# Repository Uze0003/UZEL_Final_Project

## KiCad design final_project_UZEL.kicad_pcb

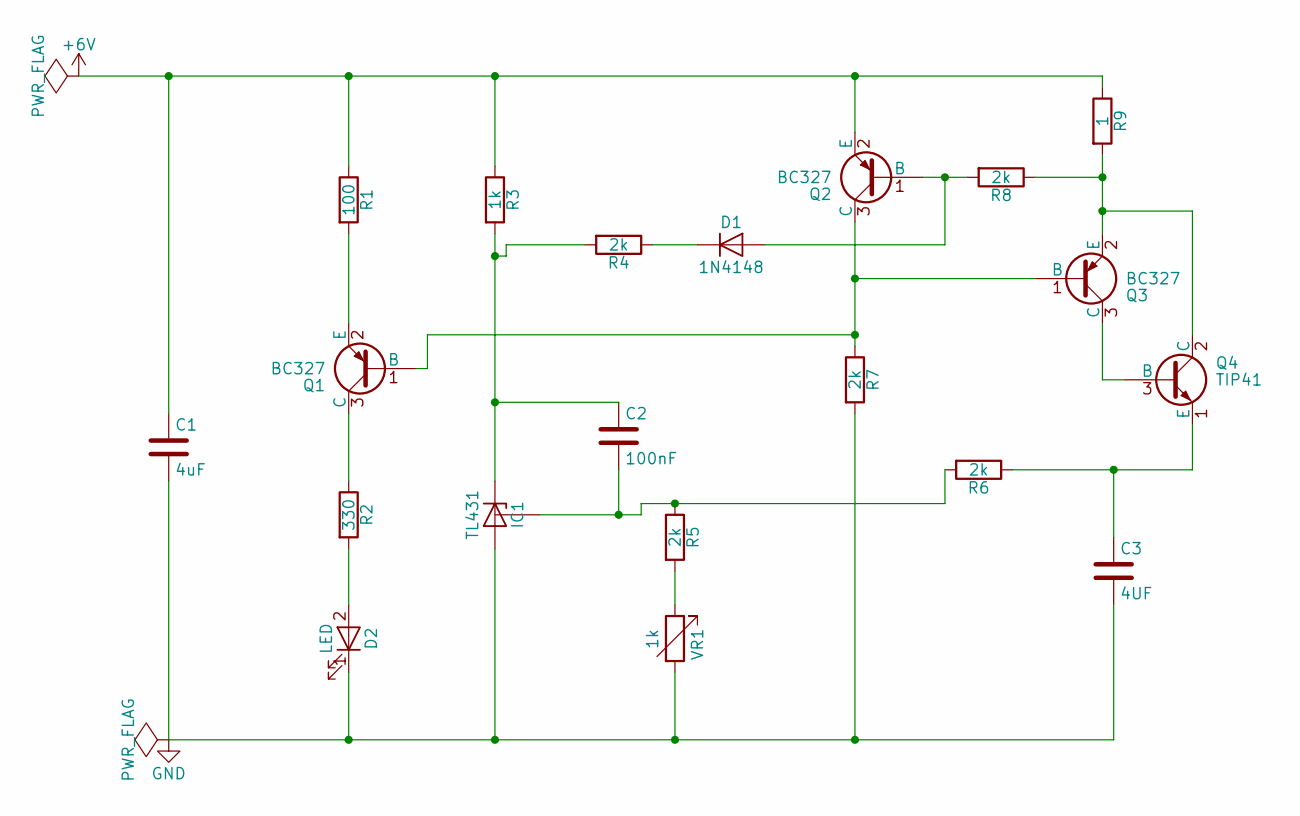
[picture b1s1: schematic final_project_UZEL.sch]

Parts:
C1: 4uF; C_Axial_L12.0mm_D6.5mm_P15.00mm_Horizontal
C2: 100nF; CP_Axial_L11.0mm_D8.0mm_P15.00mm_Horizontal
C3: 4UF; C_Axial_L12.0mm_D6.5mm_P15.00mm_Horizontal
D1: 1N4148; D_DO-15_P10.16mm_Horizontal
D2: LED; TL431-THT
IC1: TL431; D_A-405_P10.16mm_Horizontal
Q1, Q2, Q3: BC327; OldSowjetaera_Transistor_Type-I_BigPads
Q4: TIP41; OldSowjetaera_Transistor_Type-II_SmallPads
R1: 100; R_Axial_DIN0207_L6.3mm_D2.5mm_P10.16mm_Horizontal
R2: 330; R_Axial_DIN0309_L9.0mm_D3.2mm_P12.70mm_Horizontal
R3: 1k; R_Axial_DIN0207_L6.3mm_D2.5mm_P7.62mm_Horizontal
R4, R6, R7, R8: 2k; R_Axial_DIN0309_L9.0mm_D3.2mm_P5.08mm_Vertical
R5: 2k; R_Axial_DIN0204_L3.6mm_D1.6mm_P5.08mm_Vertical
R9: 1; R_Axial_DIN0204_L3.6mm_D1.6mm_P5.08mm_Horizontal
VR1: 1k; Potentiometer_Trimmer_Piher_PT-15v15_Horizontal_Px15.0mm_Py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

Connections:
+6V: C1.1, Q2.2 (E), R1.1, R3.1, R9.1
GND: C1.2, C3.2, D2.1 (K), IC1.2 (A), R7.2, VR1.2
unnamed: C2.1, IC1.1 (K), R3.2, R4.2
unnamed: C2.2, IC1.~, R5.1, R6.2
unnamed: C3.1, Q4.1 (E), R6.1
unnamed: D1.1 (K), R4.1
unnamed: D1.2 (A), Q2.1 (B), R8.2
unnamed: D2.2 (A), R2.2
unnamed: Q1.1 (B), Q2.3 (C), Q3.1 (B), R7.1
unnamed: Q1.2 (E), R1.2
unnamed: Q1.3 (C), R2.1
unnamed: Q3.2 (E), Q4.2 (C), R8.1, R9.2
unnamed: Q3.3 (C), Q4.3 (B)
unnamed: R5.2, VR1.1

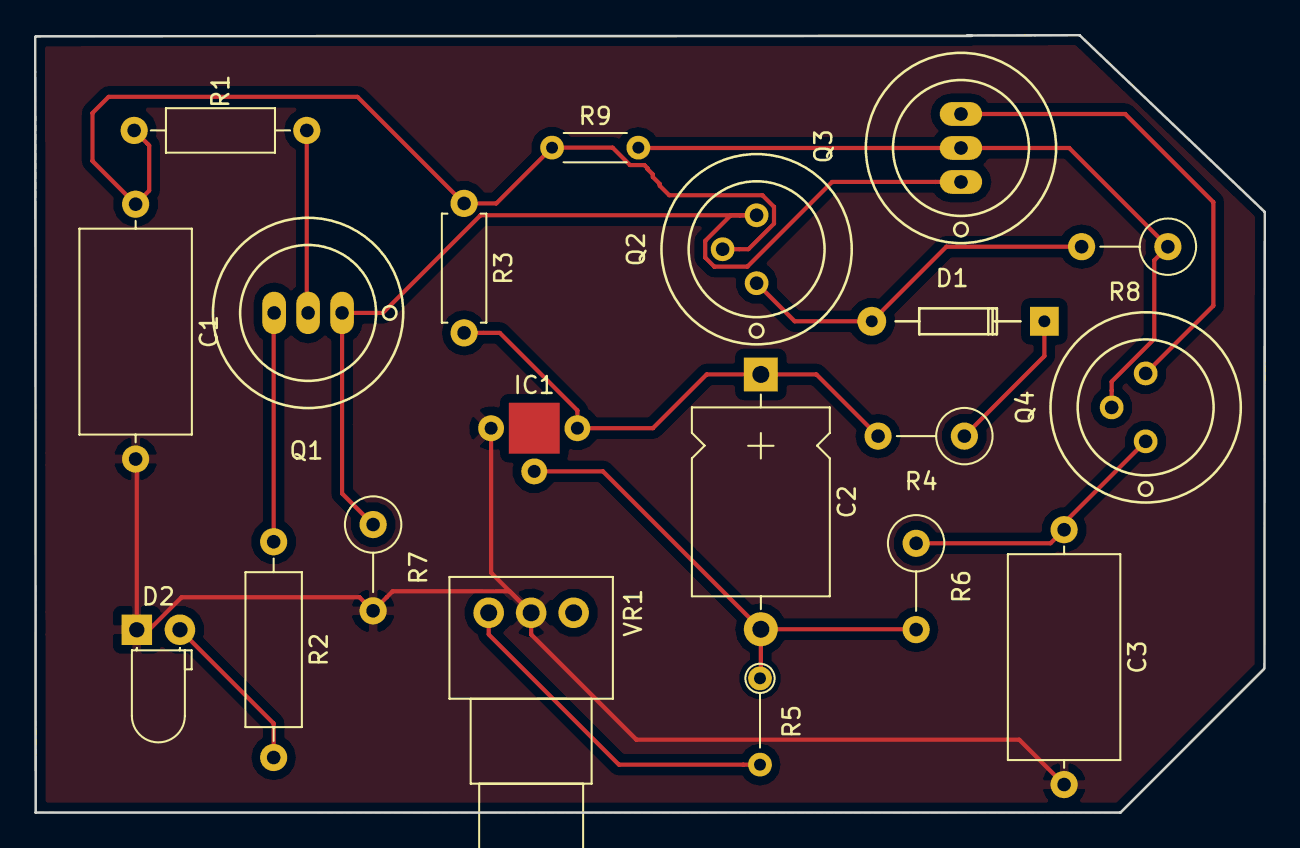
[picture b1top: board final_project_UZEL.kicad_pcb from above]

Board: 2 copper layers, 72.4 x 45.8 mm, 20 parts (0 on the bottom side), 14 nets.

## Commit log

2017-06-09 Final Project
